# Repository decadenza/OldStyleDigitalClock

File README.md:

# Old Style Digital Clock
A simple, fully functional digital clock without microcontrollers.

## Features
- HH:MM 24-hour format.
- Based on common and readily available components like counters and logic gates.
- This clock uses a Pierce oscillator circuit (quartz crystal), so it will keep the time much more accurately than a NE555 or similar timers.
- Powered by USB C female port.
- 2 x USB A ports for charging other devices (as dedicated charging ports - DCPs).
- Dimmable LEDs and self-adjusting brightness.

### LED brightness control
LEDs may result too faint in daylight and too bright at night. Therefore brightness is controlled by pulse-width modulation (PWM) and a potentiometer to adjust the duty cycle.
Furthermore, a light-dependent resistor (LDR) is introduced to automatically reduce the duty cycle at night.

The signal measured at one active LED segment is a square wave of a frequency > 30 Hz so that human eye cannot notice the flickering:

You may notice flickering if you use a camera to look at the clock. If this is a concern, you may reduce the C13 capacitor value to increase the frequency to the desired level. Full details in the schematics.

## PCB printing
A standard 2-layer PCB is used. You may generate the necessary Gerber and drill files using KiCad according to the specs of your supplier.

## 3D models
The clock may be completed by printing the case. See [3D printed parts](3DPrintedParts) folder. 

## License
This project is licensed under the **CC BY-NC-SA 4.0** license.  
© 2025 Pasquale Lafiosca

For more details, see the [LICENSE](LICENSE) file.

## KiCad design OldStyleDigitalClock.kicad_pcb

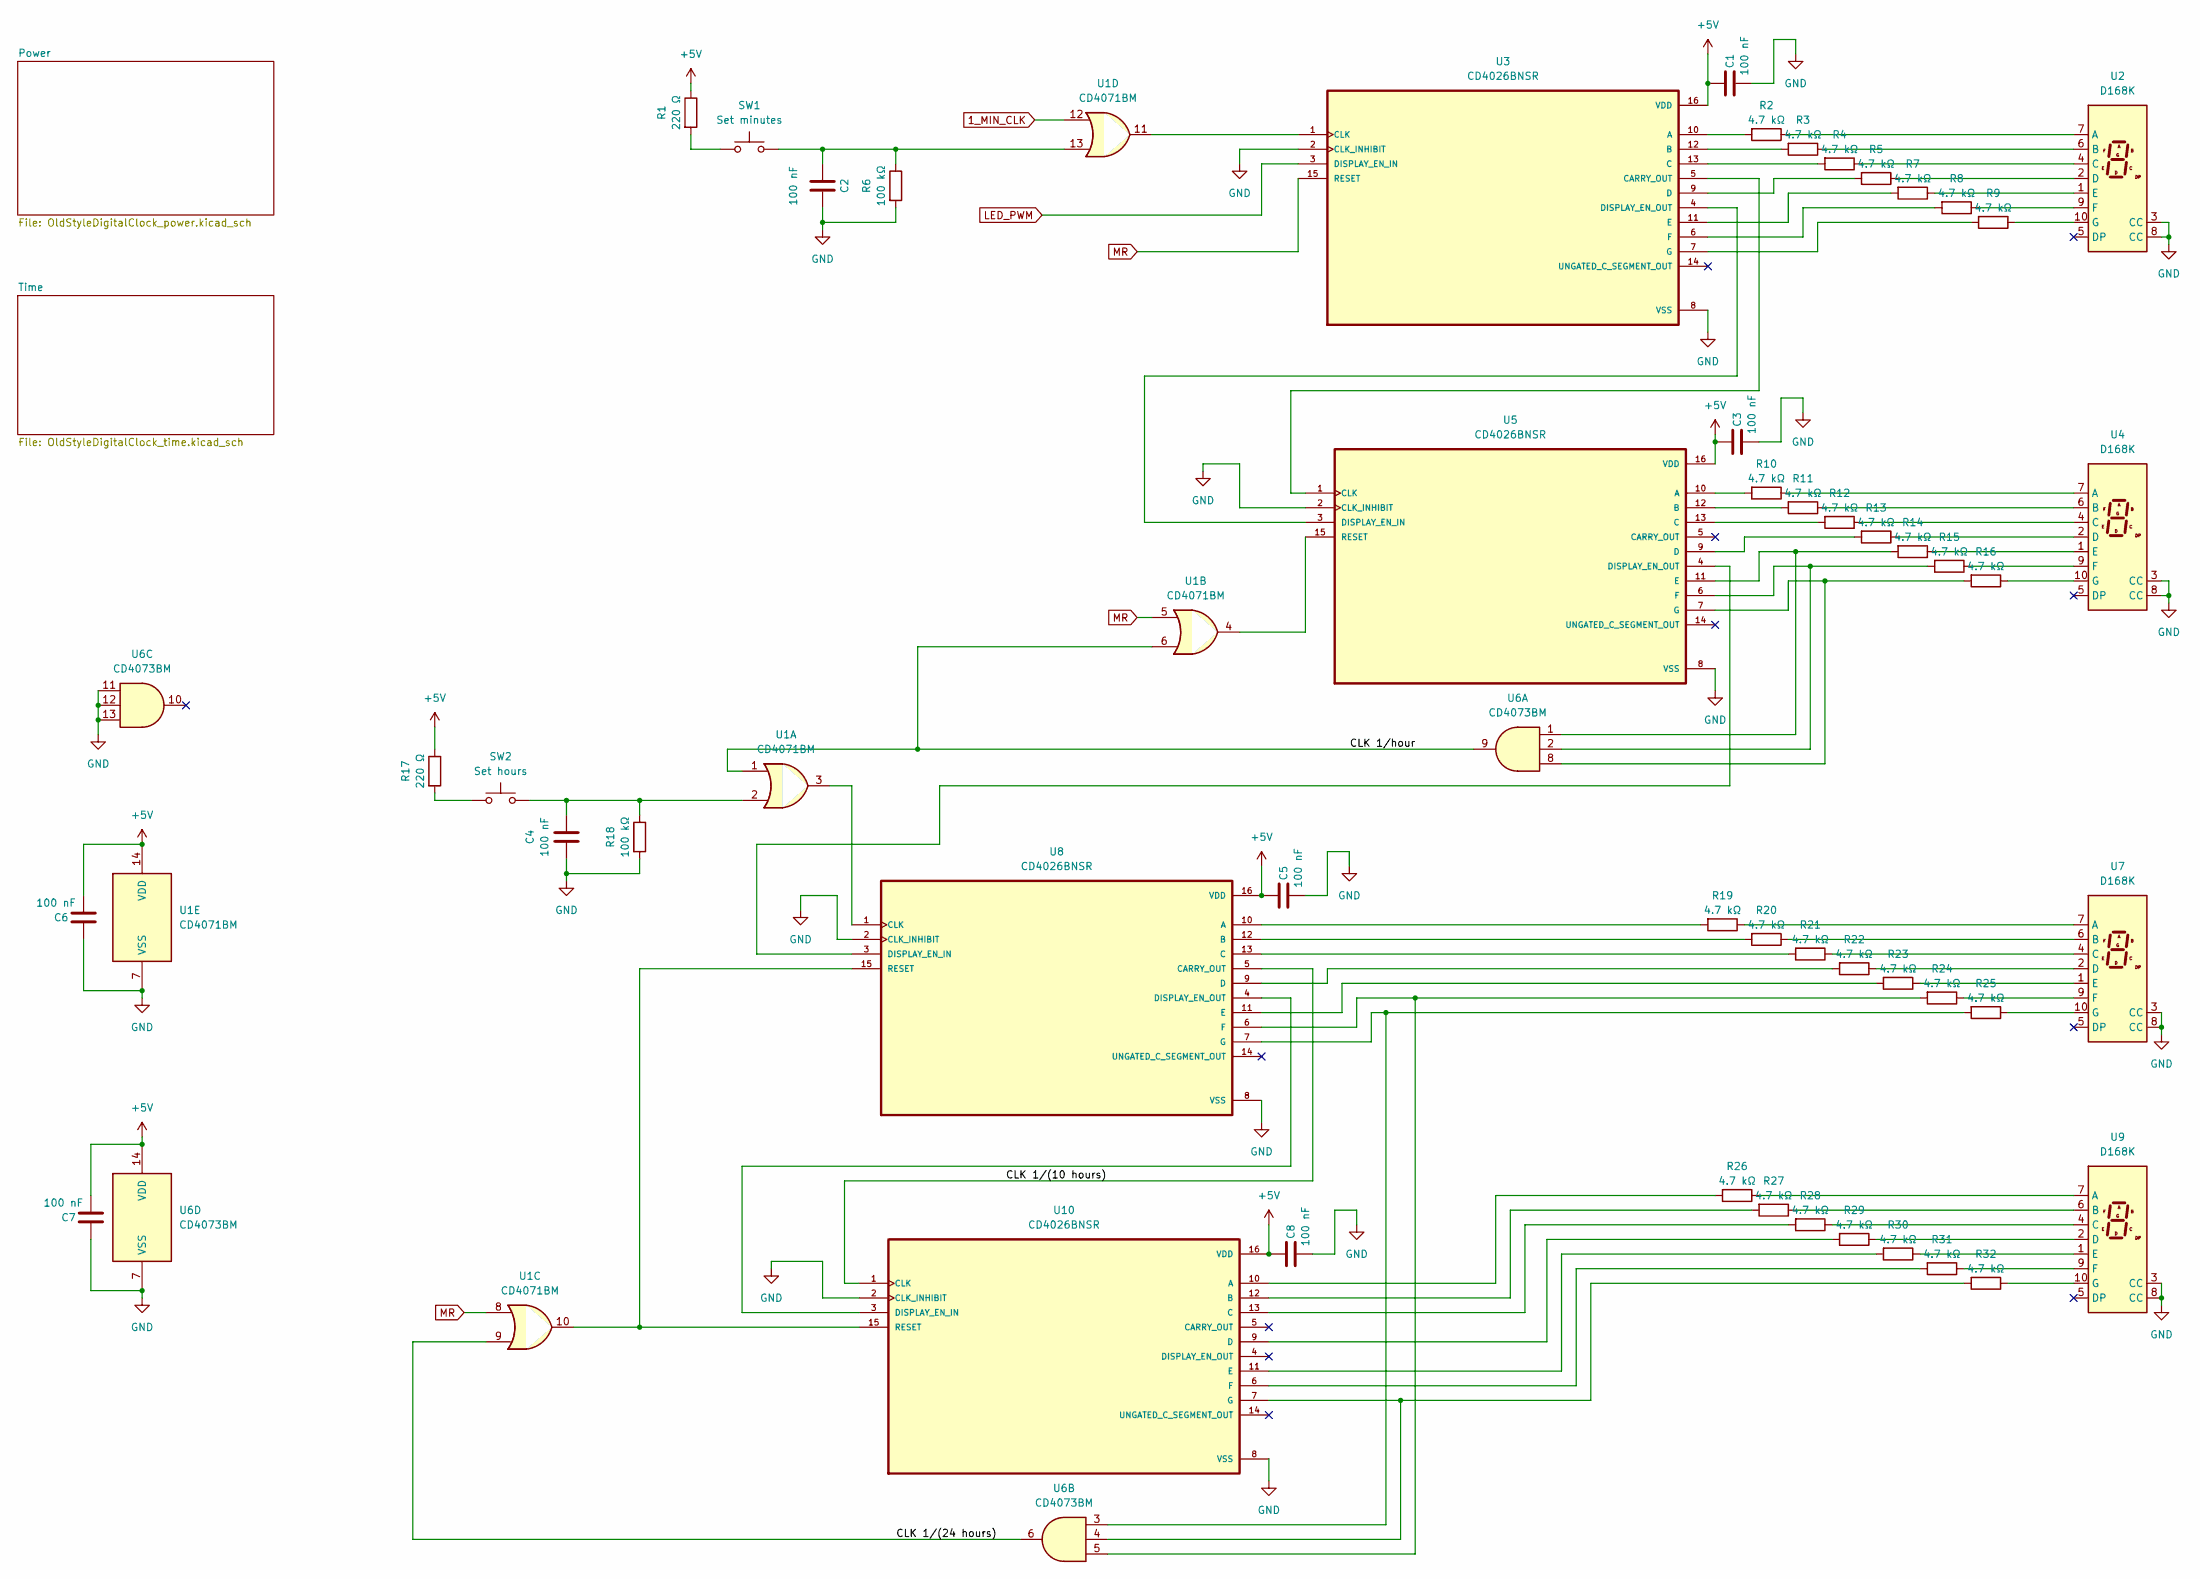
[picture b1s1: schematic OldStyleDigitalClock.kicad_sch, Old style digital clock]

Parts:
C1, C2, C3, C4, C5, C6, C7, C8: 100 nF; C_1206_3216Metric
R1, R17: 220 Ω; R_1206_3216Metric
R2, R3, R4, R5, R7, R8, R9, R10, R11, R12, R13, R14, R15, R16, R19, R20, R21, R22, R23, R24, R25, R26, R27, R28, R29, R30, R31, R32: 4.7 kΩ; R_1206_3216Metric
R6, R18: 100 kΩ; R_1206_3216Metric
SW1: Set minutes; SW_PUSH_6mm
SW2: Set hours; SW_PUSH_6mm
U1: CD4071BM; SOIC-14_3.9x8.7mm_P1.27mm
U2, U4, U7, U9: D168K; D1X8K
U3, U5, U8, U10: CD4026BNSR; SOIC-16W_5.3x10.2mm_P1.27mm
U6: CD4073BM; SOIC-14_3.9x8.7mm_P1.27mm

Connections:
1_MIN_CLK: U1.12; also elsewhere on the board
+5V: C1.1, C3.1, C5.1, C6.2, C7.2, C8.1, R1.1, R17.1, U1.14 (VDD), U3.16 (VDD), U5.16 (VDD), U6.14 (VDD), U8.16 (VDD), U10.16 (VDD); also elsewhere on the board
/CLK 1/(10 hours): U8.5 (CARRY_OUT), U10.1 (CLK)
/CLK 1/(24 hours): U1.9, U6.6
/CLK 1/hour: U1.1, U1.6, U6.9
GND: C1.2, C2.1, C3.2, C4.1, C5.2, C6.1, C7.1, C8.2, R6.2, R18.2, U1.7 (VSS), U2.3 (CC), U2.8 (CC), U3.2 (CLK_INHIBIT), U3.8 (VSS), U4.3 (CC), U4.8 (CC), U5.2 (CLK_INHIBIT), U5.8 (VSS), U6.7 (VSS), U6.11, U6.12, U6.13, U7.3 (CC), U7.8 (CC), U8.2 (CLK_INHIBIT), U8.8 (VSS), U9.3 (CC), U9.8 (CC), U10.2 (CLK_INHIBIT), U10.8 (VSS); also elsewhere on the board
LED_PWM: U3.3 (DISPLAY_EN_IN); also elsewhere on the board
MR: U1.5, U1.8, U3.15 (RESET); also elsewhere on the board
unnamed: C2.2, R6.1, SW1.2, U1.13
unnamed: C4.2, R18.1, SW2.2, U1.2
unnamed: R1.2, SW1.1
unnamed: R17.2, SW2.1
unnamed: R2.1, U2.7 (A)
unnamed: R3.1, U2.6 (B)
unnamed: R4.1, U2.4 (C)
unnamed: R5.1, U2.2 (D)
unnamed: R7.1, U2.1 (E)
unnamed: R8.1, U2.9 (F)
unnamed: R9.1, U2.10 (G)
unnamed: R2.2, U3.10 (A)
unnamed: R3.2, U3.12 (B)
unnamed: R4.2, U3.13 (C)
unnamed: U3.5 (CARRY_OUT), U5.1 (CLK)
unnamed: U1.11, U3.1 (CLK)
unnamed: R5.2, U3.9 (D)
unnamed: U3.4 (DISPLAY_EN_OUT), U5.3 (DISPLAY_EN_IN)
unnamed: R7.2, U3.11 (E)
unnamed: R8.2, U3.6 (F)
unnamed: R9.2, U3.7 (G)
unnamed: R10.1, U4.7 (A)
unnamed: R11.1, U4.6 (B)
unnamed: R12.1, U4.4 (C)
unnamed: R13.1, U4.2 (D)
unnamed: R14.1, U4.1 (E)
unnamed: R15.1, U4.9 (F)
unnamed: R16.1, U4.10 (G)
unnamed: R10.2, U5.10 (A)
unnamed: R11.2, U5.12 (B)
unnamed: R12.2, U5.13 (C)
unnamed: R13.2, U5.9 (D)
unnamed: U5.4 (DISPLAY_EN_OUT), U8.3 (DISPLAY_EN_IN)
unnamed: R14.2, U5.11 (E), U6.1
unnamed: R15.2, U5.6 (F), U6.2
unnamed: R16.2, U5.7 (G), U6.8
unnamed: U1.4, U5.15 (RESET)
unnamed: R19.1, U7.7 (A)
unnamed: R20.1, U7.6 (B)
unnamed: R21.1, U7.4 (C)
unnamed: R22.1, U7.2 (D)
unnamed: R23.1, U7.1 (E)
unnamed: R24.1, U7.9 (F)
unnamed: R25.1, U7.10 (G)
unnamed: R19.2, U8.10 (A)
unnamed: R20.2, U8.12 (B)
unnamed: R21.2, U8.13 (C)
unnamed: U1.3, U8.1 (CLK)
unnamed: R22.2, U8.9 (D)
unnamed: R23.2, U8.11 (E)
unnamed: R24.2, U6.5, U8.6 (F)
unnamed: R25.2, U6.3, U8.7 (G)
unnamed: R26.1, U9.7 (A)
unnamed: R27.1, U9.6 (B)
unnamed: R28.1, U9.4 (C)
unnamed: R29.1, U9.2 (D)
unnamed: R30.1, U9.1 (E)
unnamed: R31.1, U9.9 (F)
unnamed: R32.1, U9.10 (G)
unnamed: R26.2, U10.10 (A)
unnamed: R27.2, U10.12 (B)
unnamed: R28.2, U10.13 (C)
unnamed: R29.2, U10.9 (D)
unnamed: U8.4 (DISPLAY_EN_OUT), U10.3 (DISPLAY_EN_IN)
unnamed: R30.2, U10.11 (E)
unnamed: R31.2, U10.6 (F)
unnamed: R32.2, U6.4, U10.7 (G)
unnamed: U1.10, U8.15 (RESET), U10.15 (RESET)

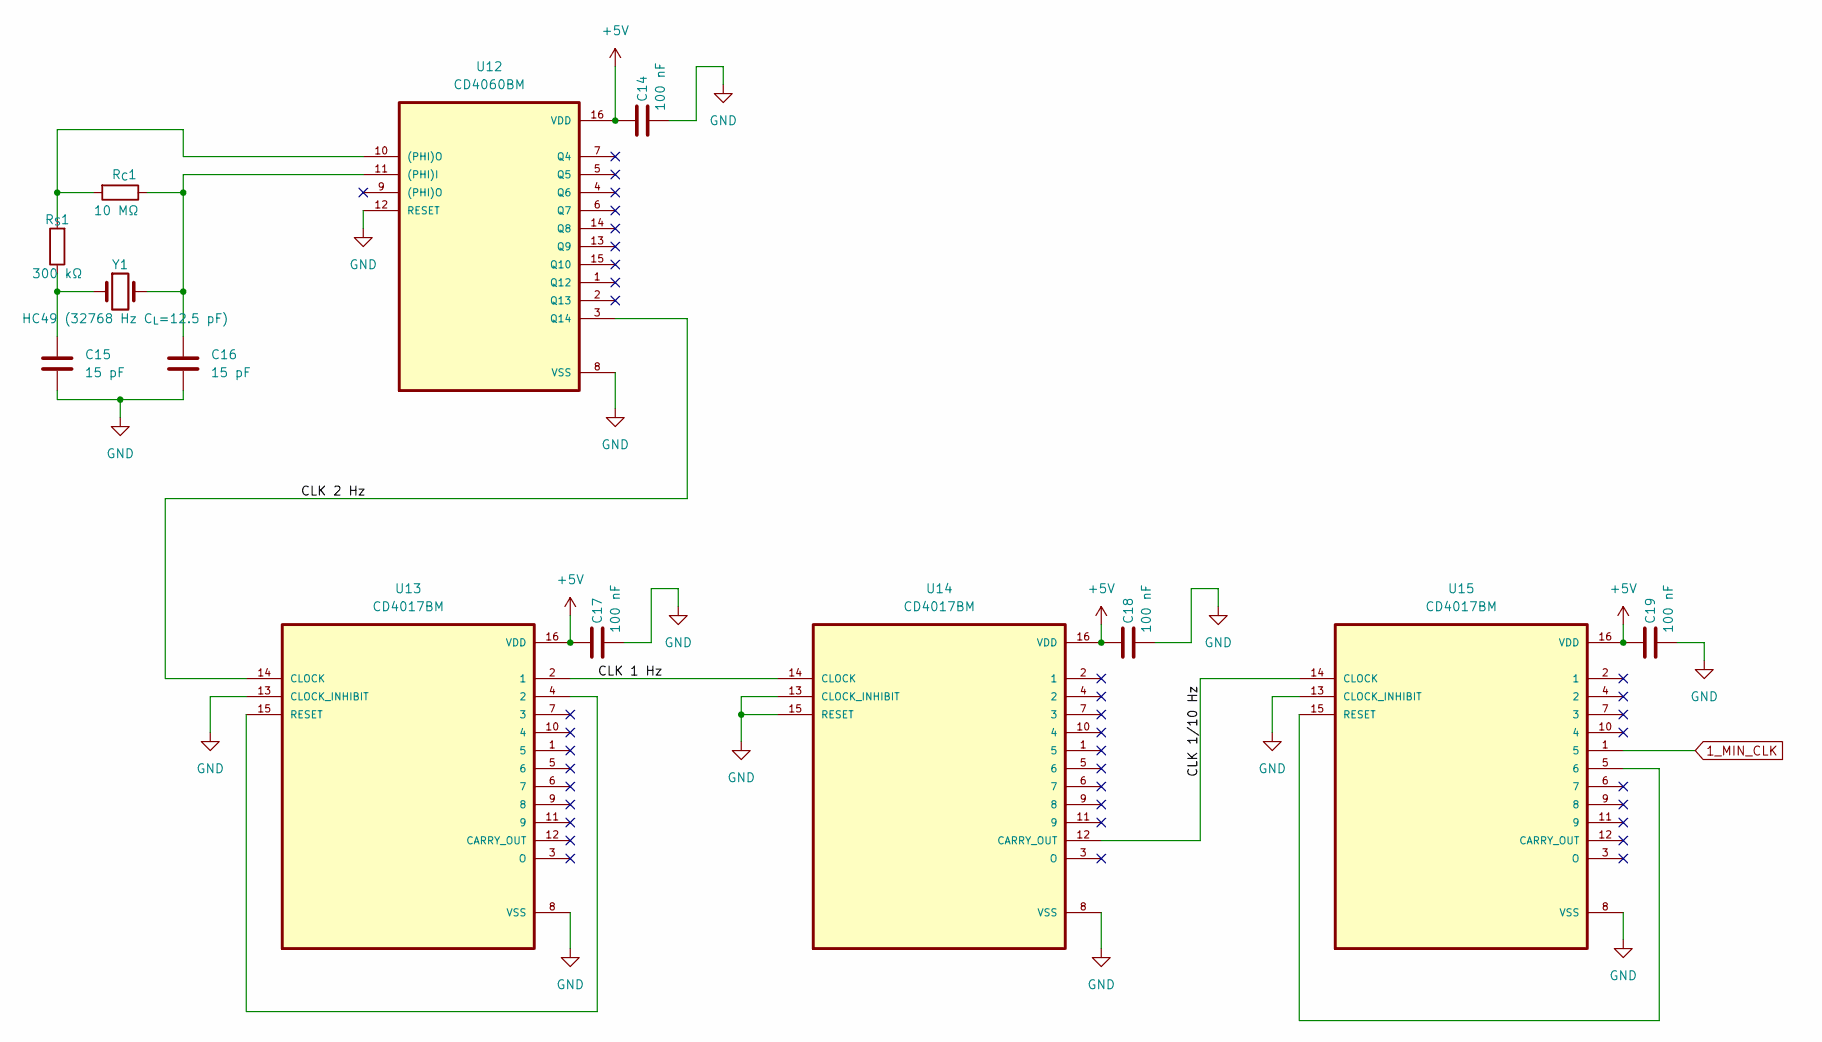
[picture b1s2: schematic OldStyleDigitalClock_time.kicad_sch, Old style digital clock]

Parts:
C14, C17, C18, C19: 100 nF; C_1206_3216Metric
C15, C16: 15 pF; C_1206_3216Metric
R_{C}1: 10 MΩ; R_1206_3216Metric
R_{S}1: 300 kΩ; R_1206_3216Metric
U12: CD4060BM; SOIC-16_3.9x9.9mm_P1.27mm
U13, U14, U15: CD4017BM; SOIC-16_3.9x9.9mm_P1.27mm
Y1: HC49 (32768 Hz C_{L}=12.5 pF); Crystal_AT310_D3.0mm_L10.0mm_Horizontal

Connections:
1_MIN_CLK: U15.1 (5); also elsewhere on the board
+5V: C14.1, C17.1, C18.1, C19.1, U12.16 (VDD), U13.16 (VDD), U14.16 (VDD), U15.16 (VDD); also elsewhere on the board
/Time/CLK 1 Hz: U13.2 (1), U14.14 (CLOCK)
/Time/CLK 1/10 Hz: U14.12 (CARRY_OUT), U15.14 (CLOCK)
/Time/CLK 2 Hz: U12.3 (Q14), U13.14 (CLOCK)
GND: C14.2, C15.2, C16.2, C17.2, C18.2, C19.2, U12.8 (VSS), U12.12 (RESET), U13.8 (VSS), U13.13 (CLOCK_INHIBIT), U14.8 (VSS), U14.13 (CLOCK_INHIBIT), U14.15 (RESET), U15.8 (VSS), U15.13 (CLOCK_INHIBIT); also elsewhere on the board
unnamed: C15.1, R_{S}1.1, Y1.1
unnamed: R_{C}1.2, R_{S}1.2, U12.10 ((PHI)O)
unnamed: C16.1, R_{C}1.1, U12.11 ((PHI)I), Y1.2
unnamed: U13.4 (2), U13.15 (RESET)
unnamed: U15.5 (6), U15.15 (RESET)

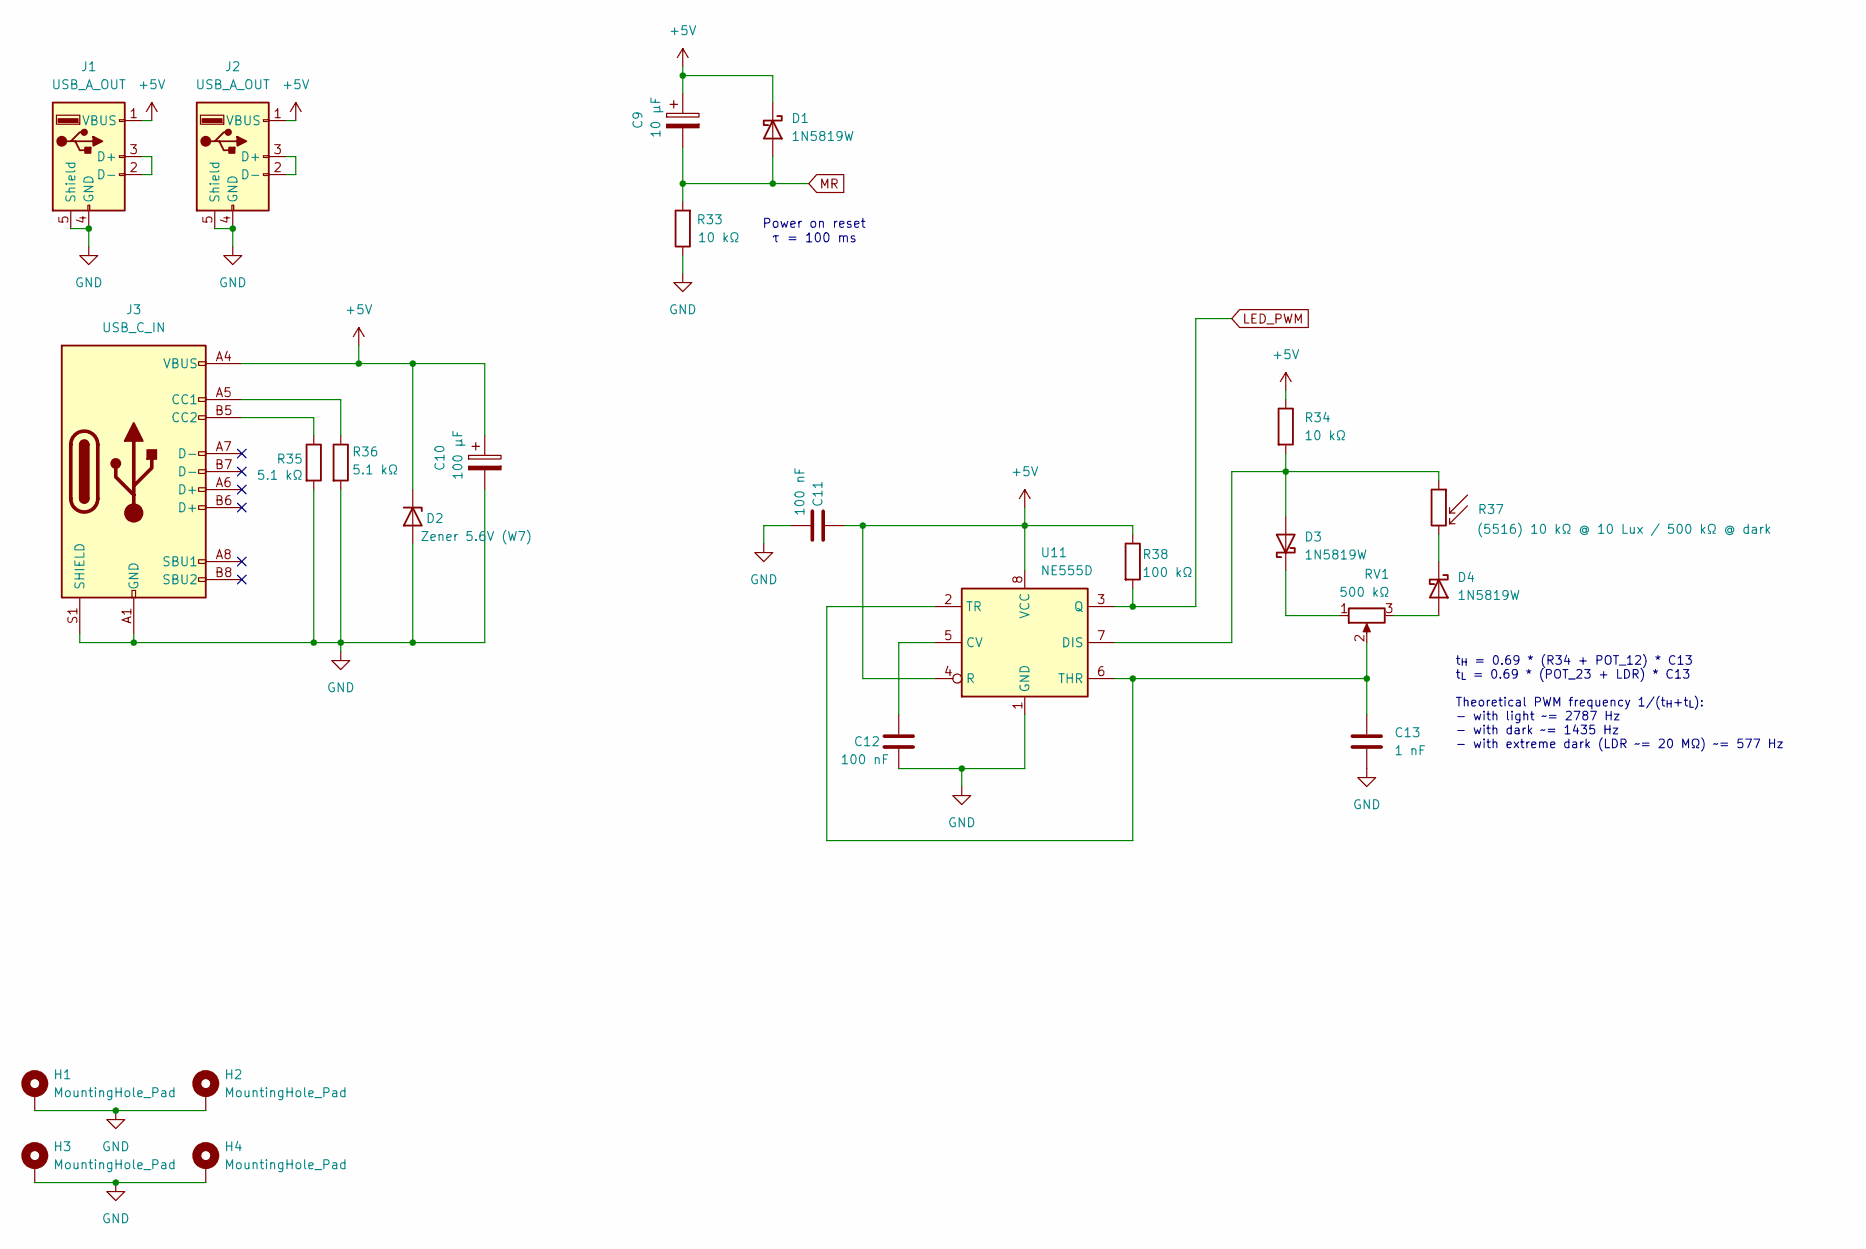
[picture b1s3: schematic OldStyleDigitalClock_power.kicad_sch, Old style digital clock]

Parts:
C9: 10 µF; CP_Radial_D6.3mm_P2.50mm
C10: 100 µF; CP_Radial_D6.3mm_P2.50mm
C11, C12: 100 nF; C_1206_3216Metric
C13: 1 nF; C_1206_3216Metric
D1, D3, D4: 1N5819W; D_SOD-123
D2: Zener 5.6V (W7); D_SOD-123
H1, H2, H3, H4: MountingHole_Pad; MountingHole_2.2mm_M2_DIN965_Pad
J1, J2: USB_A_OUT; USB_A_Molex_67643_Horizontal
J3: USB_C_IN; USB_C_Receptacle_XKB_U262-16XN-4BVC11
R33, R34: 10 kΩ; R_1206_3216Metric
R35, R36: 5.1 kΩ; R_1206_3216Metric
R37: (5516) 10 kΩ @ 10 Lux / 500 kΩ @ dark; R_LDR_5.1x4.3mm_P3.4mm_Vertical
R38: 100 kΩ; R_1206_3216Metric
RV1: 500 kΩ; Potentiometer_Alps_RK163_Single_Horizontal
U11: NE555D; SOIC-8_3.9x4.9mm_P1.27mm

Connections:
+5V: C9.1, C10.1, C11.1, D1.1 (K), D2.1 (K), J1.1 (VBUS), J2.1 (VBUS), J3.A4 (VBUS), J3.A9 (VBUS), J3.B4 (VBUS), J3.B9 (VBUS), R34.1, R38.1, U11.4 (R), U11.8 (VCC); also elsewhere on the board
GND: C10.2, C11.2, C12.2, C13.2, D2.2 (A), H1.1, H2.1, H3.1, H4.1, J1.4 (GND), J1.5 (Shield), J2.4 (GND), J2.5 (Shield), J3.A1 (GND), J3.A12 (GND), J3.B1 (GND), J3.B12 (GND), J3.S1 (SHIELD), R33.1, R35.2, R36.2, U11.1 (GND); also elsewhere on the board
LED_PWM: R38.2, U11.3 (Q); also elsewhere on the board
MR: C9.2, D1.2 (A), R33.2; also elsewhere on the board
unnamed: D3.2 (A), R34.2, R37.1, U11.7 (DIS)
unnamed: D3.1 (K), RV1.1
unnamed: D4.2 (A), RV1.3
unnamed: D4.1 (K), R37.2
unnamed: J1.2 (D-), J1.3 (D+)
unnamed: J2.2 (D-), J2.3 (D+)
unnamed: J3.A5 (CC1), R36.1
unnamed: J3.B5 (CC2), R35.1
unnamed: C12.1, U11.5 (CV)
unnamed: C13.1, RV1.2, U11.2 (TR), U11.6 (THR)

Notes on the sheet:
Power on reset τ = 100 ms
t_{H} = 0.69 * (R34 + POT_12) * C13 t_{L} = 0.69 * (POT_23 + LDR) * C13 Theoretical PWM frequency 1/(t_{H}+t_{L}): - with light ~= 2787 Hz - with dark ~= 1435 Hz - with extreme dark (LDR ~= 20 MΩ) ~= 577 Hz

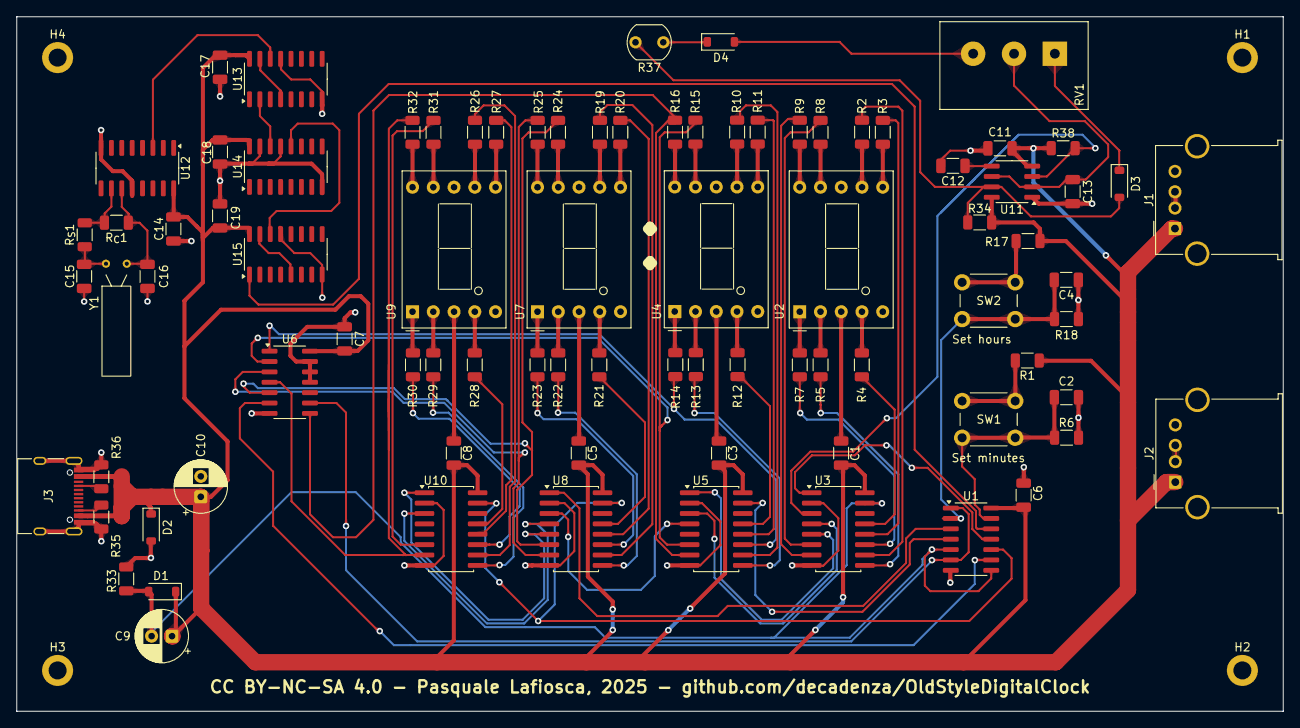
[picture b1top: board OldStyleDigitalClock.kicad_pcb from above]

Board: 2 copper layers, 155.0 x 85.0 mm, 89 parts (0 on the bottom side), 94 nets.

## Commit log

2025-05-18 Update README.md
    Using American spelling.
2025-05-18 Uploaded project files
2025-05-18 Added 3D printed stand and solar panel support
2025-05-18 Added fabrication output file
2025-05-18 Added PCN info in README.md
2025-05-18 Corrected 3D parts, added Blender file
2025-05-18 Corrected typo
2025-05-19 Added PDF schematics
2025-05-19 Added image
2025-05-31 Added gitignore
2025-05-31 Using 5 V solar cell instead of 4 V, as more appropriate for indoor situations
2025-08-17 Added different vertical and horizontal supports
2025-08-17 Using 512 Hz clock signal to rapidly turn on and off the LEDs via the CD4026 display enable pin, both saving 50% power and hopefully improving the battery charging. The LED attenuation is negligible.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
2025-08-24 Updated README with explanation of latest changes
2025-09-29 Using 512 Hz clock signal to rapidly turn on and off the LEDs via the CD4026 display enable pin, both saving 50% power and hopefully improving the battery charging. The LED attenuation is negligible.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
2025-09-30 Corrected LED display enable signal and decreased to 64 Hz to reduce capacitance and save power without any flickering visible
2025-10-11 Removed batteries and added USB connectors. One USB C for power in, two usb A power outlets. Pre-routing.
2025-10-12 Introducing PWM for dimmable LEDs
2025-10-13 Using standard astable multivibrator for LED dimming
2025-10-13 Added photoresistor for automatic brightness adjustment
2025-10-16 Comment
2025-10-16 Minor change to avoid issue with hours not changing
2025-10-17 Using OR gates instead of diodes. Changed POT for 555
2025-10-19 Updated PWM calculations
2025-10-20 New PWM and POT configuration
2025-10-20 Added pull up on NA555 output. Minor changes.
2025-10-20 Increased C18 value
2025-10-20 Partial commit: Moved to SMD footprints
2025-10-20 Removed old footprints
2025-10-21 Constant frequency PWM with fixed LDR value
2025-10-21 Fixed typo
2025-10-22 Assigned footprints: first draft
2025-10-23 PCB initial setup
2025-10-24 PCB alignment
2025-10-24 pcb rough organisation
2025-10-27 README draft for new USB version
2025-10-27 Tracks 1
2025-10-28 More tracks
2025-10-28 Tracks 20251028
2025-10-28 Cleaning up for new layout
2025-10-29 segment tracks started
2025-11-02 Fixed issue in MR circuit. More tracks.
2025-11-04 Tracks partial
2025-11-06 Tracks, first draft completed prior to design review
2025-11-06 connected mounting holes to GND
2025-11-06 Checked DRC, all ok except USB C clearances
2025-11-07 Reduced board size, RDC passing except for USB C clearance.
2025-11-07 Minor adjustments, moved oscillator away from mounting hole, improved some tracks.
2025-11-08 Moved USB receptacles, minor changes. Marked no connect pins.
2025-11-08 Reviewed LED limiting resistors to stay within specs
2025-11-09 Centering
2025-11-09 Redesigned USB C input in a more compact way.
2025-11-12 Changed footprints for easy to find parts
2025-11-12 Changed tracks for new IC packages
2025-11-12 Updated NE555 package
2025-11-12 Updated 4071 package
2025-11-12 Updated 4073 package
2025-11-13 Minor changes
2025-11-13 Checked all IC against database and updated exact value and footprints
2025-11-21 Minor tracks changes
2025-11-25 fixed MR circuit (again)
2025-11-25 Replaced rectifier diodes with Schottky ones
2025-11-25 Replaced diode values
2025-11-28 Cleaned up and built fabrication output with JLCPCB standards
2025-11-30 First 3D model file with PCB base.
2025-11-30 Minor LEDs centering.
2025-11-30 Added LEd volume in 3D model
2025-12-01 First front enclosure draft
2025-12-01 Preparing for nutted slots
2025-12-06 Enclosure with M3 nuts and adjusted thickness
2025-12-06 Holder back 10deg
2025-12-06 Enclosure with USB ports and buttons
2025-12-06 Added LDR top hole
2025-12-12 Adapted 3D parts to M2 bolts
2025-12-12 Corrected Zener diode specs
2025-12-14 Changed units for caps
2025-12-14 New layout for Pierce oscillator to reduce trace length and stray capacity
2025-12-16 Moved capacitors closer
2025-12-17 Updated Pierce oscillator values with working values on PCB
2025-12-21 Reduced C13 value to avoid visible flickering
2025-12-21 Added missing reset connection for low digit of the hours
2025-12-22 Added frontal hole for LDR
2025-12-22 Added front hole for LDR with open top
2025-12-22 Applied transformations, smoothing enclosure
2025-12-23 Updated fabrication output
2025-12-23 README typo
2026-01-02 Restored old Rs value of 300k
2026-01-02 Front holes and taller front enclosure
2026-01-02 Reduced front screw hole diameter
2026-01-02 Replaced enclosure support to allow shorter M2 bolts, added extra gap for usb C connector
2026-01-03 Added STL parts
2026-01-03 Reduced C13 to 4.7 nF to account for stray capacitance and avoid flickering
2026-01-03 Tracking STL parts
2026-01-03 Updated potentiometer shield
2026-01-04 Minor PCB layout change to reduce traces stray capacitance
2026-01-05 Renamed folder, removed fabrication output
2026-01-05 Updated comment
2026-01-07 Updated PWm schematics calculations
2026-01-09 Reduced C13 further while staying within the 555 limit of 100 kHz even when LDR may raise to several MΩ. This avoids flickering.
2026-01-12 Added link in PCB description
2026-01-20 Add LICENSE file with CC BY-SA 4.0
    Added Creative Commons Attribution-ShareAlike 4.0 International Public License to the project.
2026-01-20 Revise license information in README.md
    Updated license section for clarity and formatting.
2026-02-21 Minor change to 3d pot shield

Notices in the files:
OldStyleDigitalClock.kicad_pcb:
CC BY-NC-SA 4.0 - Pasquale Lafiosca, 2025 - github.com/decadenza/OldStyleDigitalClock
